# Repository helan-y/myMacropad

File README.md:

# myMacropad

## Features!
This mainly exists for easier volume and brightness control. 
- Left Knob: brightness, press to toggle F11.
- Right Knob: volume, press to toggle mute.
- Assorted Buttons: up, down, left, right, and space.

## PCB

Fairly simple, mildly infuriating. I still have no idea how positioning works in KiCad. At which point are the coordinates relative to?? Why is it different across different parts??

For later: 
- I want to make a little logo to put on the silkscreen! As well as get a more unified way of marking my PCBs.
- Probably clean up the wiring :\(. This is not my best work but uh it'll live and honestly I don't think signal integrity matters that much here. 

## Schematic

## CAD

## Firmware 
Uses QMK!

## BOM
- 1x XIAO RP2040
- 5x Cherry MX Switches
- 5x Blank DSA Keycaps
- 2x EC11 20mm Rotary Encoders
- 4x M3x16 Bolt
- 4x M3 Heatset

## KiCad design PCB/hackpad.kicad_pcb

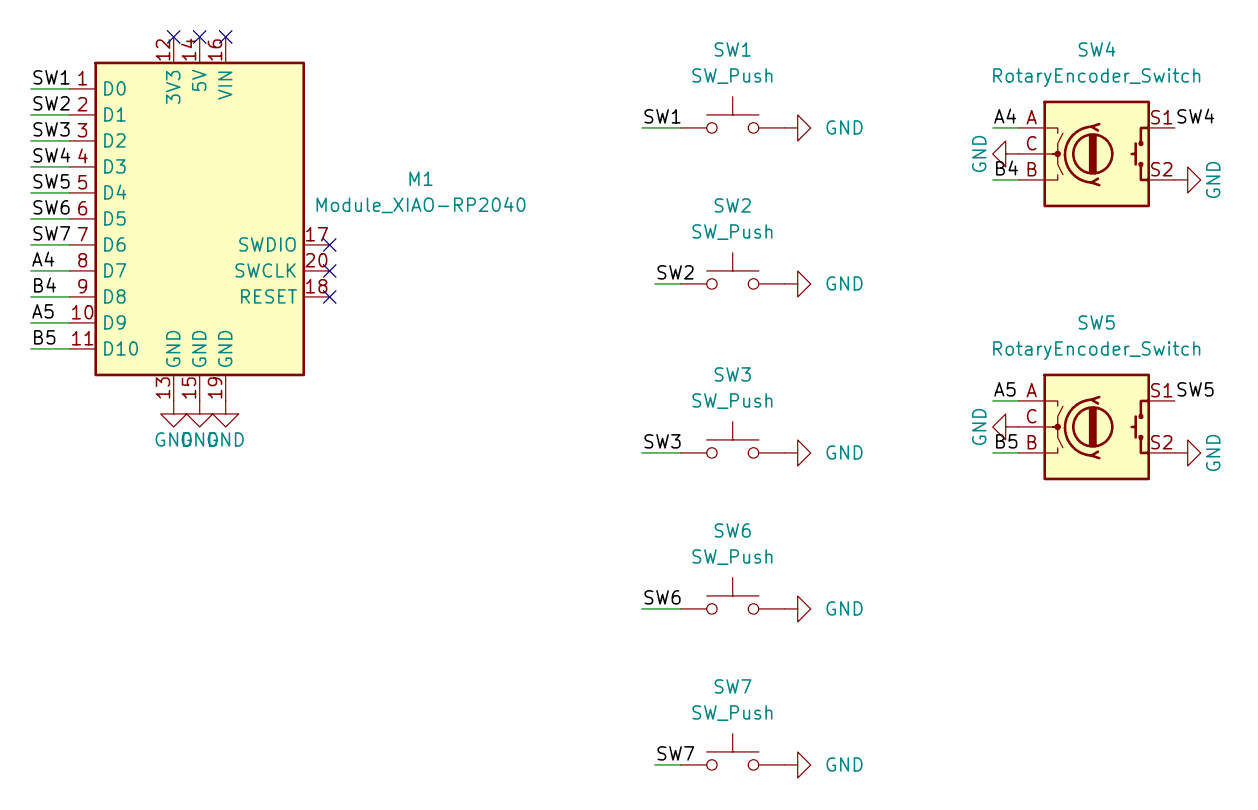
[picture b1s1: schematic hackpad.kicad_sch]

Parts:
M1: Module_XIAO-RP2040; SeeedStudio_XIAO_RP2040
SW1, SW2, SW3, SW6, SW7: SW_Push; SW_Cherry_MX_1.00u_PCB
SW4, SW5: RotaryEncoder_Switch; RotaryEncoder_Alps_EC12E-Switch_Vertical_H20mm

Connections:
/A4: M1.8 (D7), SW4.A
/A5: M1.10 (D9), SW5.A
/B4: M1.9 (D8), SW4.B
/B5: M1.11 (D10), SW5.B
/SW1: M1.1 (D0), SW1.1
/SW2: M1.2 (D1), SW2.1
/SW3: M1.3 (D2), SW3.1
/SW4: M1.4 (D3), SW4.S1
/SW5: M1.5 (D4), SW5.S1
/SW6: M1.6 (D5), SW6.1
/SW7: M1.7 (D6), SW7.1
GND: M1.13 (GND), M1.15 (GND), M1.19 (GND), SW1.2, SW2.2, SW3.2, SW4.C, SW4.S2, SW5.C, SW5.S2, SW6.2, SW7.2

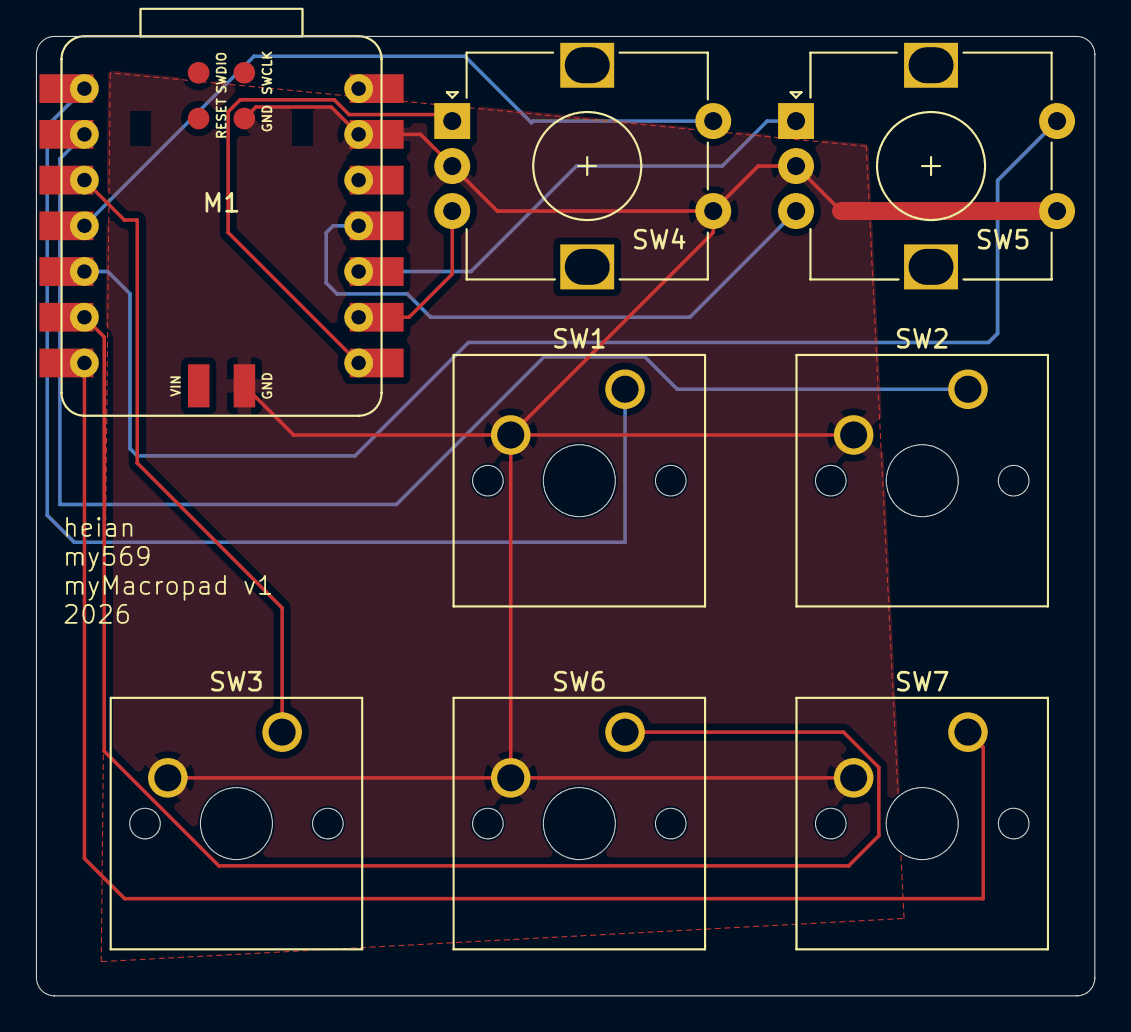
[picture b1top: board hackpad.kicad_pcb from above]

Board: 2 copper layers, 58.8 x 53.3 mm, 8 parts (0 on the bottom side), 12 nets.

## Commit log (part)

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2026-06-11 read me initial
2026-06-11 read me updates
2026-06-11 readme formating
2026-06-11 Add MIT License to the project
2026-06-11 starting cad and firmware
2026-06-11 cad and firmware
2026-06-11 cad and firmware started help
2026-06-11 cad done
2026-06-11 mesh files
2026-06-11 qmk done
2026-06-11 finished. final readme edits
2026-06-15 Add LICENSE file
